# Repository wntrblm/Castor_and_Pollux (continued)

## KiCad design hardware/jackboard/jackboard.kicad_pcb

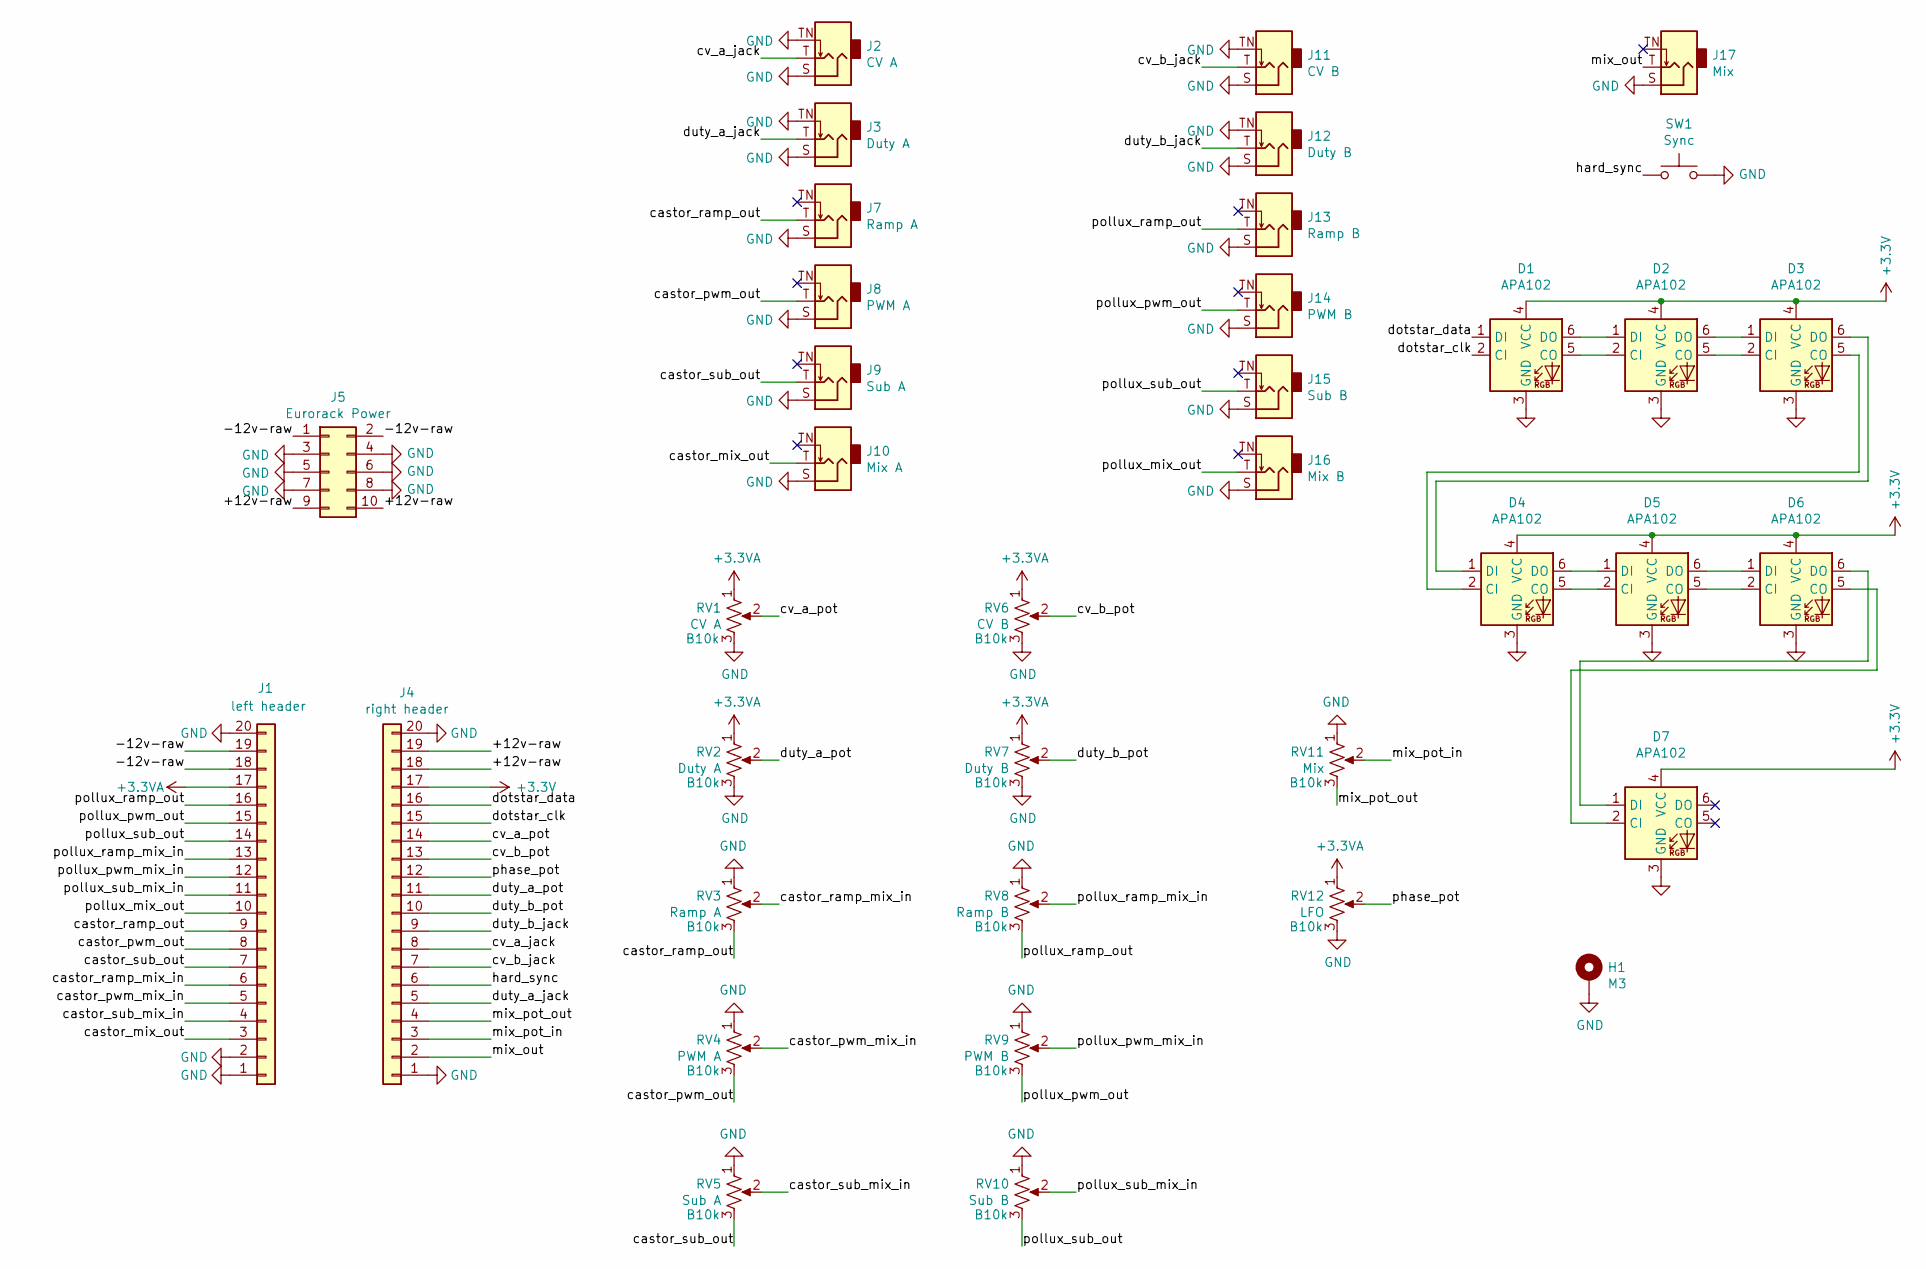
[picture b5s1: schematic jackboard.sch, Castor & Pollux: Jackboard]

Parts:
D1, D2, D3, D4, D5, D6, D7: APA102; LED_RGB_5050-6
H1: M3; MountingHole_3.2mm_M3_Pad_Via
J1: left header; PinHeader_1x20_P2.54mm_Vertical
J2: CV A; WQP-WQP518MA
J3: Duty A; WQP-WQP518MA
J4: right header; PinHeader_1x20_P2.54mm_Vertical
J5: Eurorack Power; 2X5-SHROUDED_LOCK
J7: Ramp A; WQP-WQP518MA
J8: PWM A; WQP-WQP518MA
J9: Sub A; WQP-WQP518MA
J10: Mix A; WQP-WQP518MA
J11: CV B; WQP-WQP518MA
J12: Duty B; WQP-WQP518MA
J13: Ramp B; WQP-WQP518MA
J14: PWM B; WQP-WQP518MA
J15: Sub B; WQP-WQP518MA
J16: Mix B; WQP-WQP518MA
J17: Mix; WQP-WQP518MA
RV1: CV A; Alpha_Pot
RV2: Duty A; Alpha_Pot
RV3: Ramp A; Alpha_Pot
RV4: PWM A; Alpha_Pot
RV5: Sub A; Alpha_Pot
RV6: CV B; Alpha_Pot
RV7: Duty B; Alpha_Pot
RV8: Ramp B; Alpha_Pot
RV9: PWM B; Alpha_Pot
RV10: Sub B; Alpha_Pot
RV11: Mix; Alpha_Pot
RV12: LFO; Alpha_Pot
SW1: Sync; SW_PUSH_6mm

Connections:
+3.3VA: J1.17, RV1.1, RV2.1, RV6.1, RV7.1, RV12.1
+3V3: D1.4 (VCC), D2.4 (VCC), D3.4 (VCC), D4.4 (VCC), D5.4 (VCC), D6.4 (VCC), D7.4 (VCC), J4.17
/+12v-raw: J4.18, J4.19, J5.9, J5.10
/-12v-raw: J1.18, J1.19, J5.1, J5.2
/castor_mix_out: J1.3, J10.T
/castor_pwm_mix_in: J1.5, RV4.2
/castor_pwm_out: J1.8, J8.T, RV4.3
/castor_ramp_mix_in: J1.6, RV3.2
/castor_ramp_out: J1.9, J7.T, RV3.3
/castor_sub_mix_in: J1.4, RV5.2
/castor_sub_out: J1.7, J9.T, RV5.3
/cv_a_jack: J2.T, J4.8
/cv_a_pot: J4.14, RV1.2
/cv_b_jack: J4.7, J11.T
/cv_b_pot: J4.13, RV6.2
/dotstar_clk: D1.2 (CI), J4.15
/dotstar_data: D1.1 (DI), J4.16
/duty_a_jack: J3.T, J4.5
/duty_a_pot: J4.11, RV2.2
/duty_b_jack: J4.9, J12.T
/duty_b_pot: J4.10, RV7.2
/hard_sync: J4.6, SW1.1
/mix_out: J4.2, J17.T
/mix_pot_in: J4.3, RV11.2
/mix_pot_out: J4.4, RV11.3
/phase_pot: J4.12, RV12.2
/pollux_mix_out: J1.10, J16.T
/pollux_pwm_mix_in: J1.12, RV9.2
/pollux_pwm_out: J1.15, J14.T, RV9.3
/pollux_ramp_mix_in: J1.13, RV8.2
/pollux_ramp_out: J1.16, J13.T, RV8.3
/pollux_sub_mix_in: J1.11, RV10.2
/pollux_sub_out: J1.14, J15.T, RV10.3
GND: D1.3 (GND), D2.3 (GND), D3.3 (GND), D4.3 (GND), D5.3 (GND), D6.3 (GND), D7.3 (GND), H1.1, J1.1, J1.2, J1.20, J2.S, J2.TN, J3.S, J3.TN, J4.1, J4.20, J5.3, J5.4, J5.5, J5.6, J5.7, J5.8, J7.S, J8.S, J9.S, J10.S, J11.S, J11.TN, J12.S, J12.TN, J13.S, J14.S, J15.S, J16.S, J17.S, RV1.3, RV2.3, RV3.1, RV4.1, RV5.1, RV6.3, RV7.3, RV8.1, RV9.1, RV10.1, RV11.1, RV12.3, SW1.2
unnamed: D1.5 (CO), D2.2 (CI)
unnamed: D1.6 (DO), D2.1 (DI)
unnamed: D2.5 (CO), D3.2 (CI)
unnamed: D2.6 (DO), D3.1 (DI)
unnamed: D3.5 (CO), D4.2 (CI)
unnamed: D3.6 (DO), D4.1 (DI)
unnamed: D4.5 (CO), D5.2 (CI)
unnamed: D4.6 (DO), D5.1 (DI)
unnamed: D5.5 (CO), D6.2 (CI)
unnamed: D5.6 (DO), D6.1 (DI)
unnamed: D6.5 (CO), D7.2 (CI)
unnamed: D6.6 (DO), D7.1 (DI)

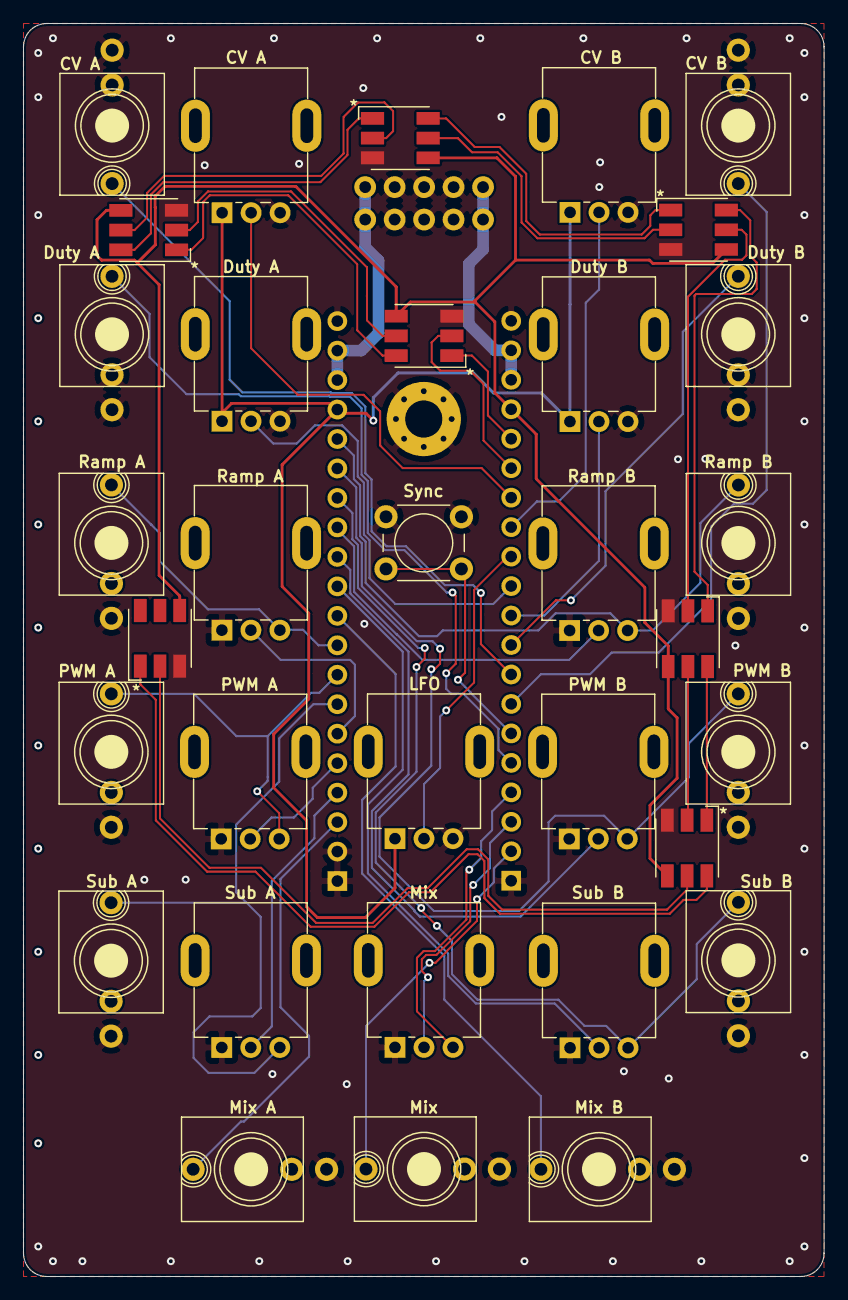
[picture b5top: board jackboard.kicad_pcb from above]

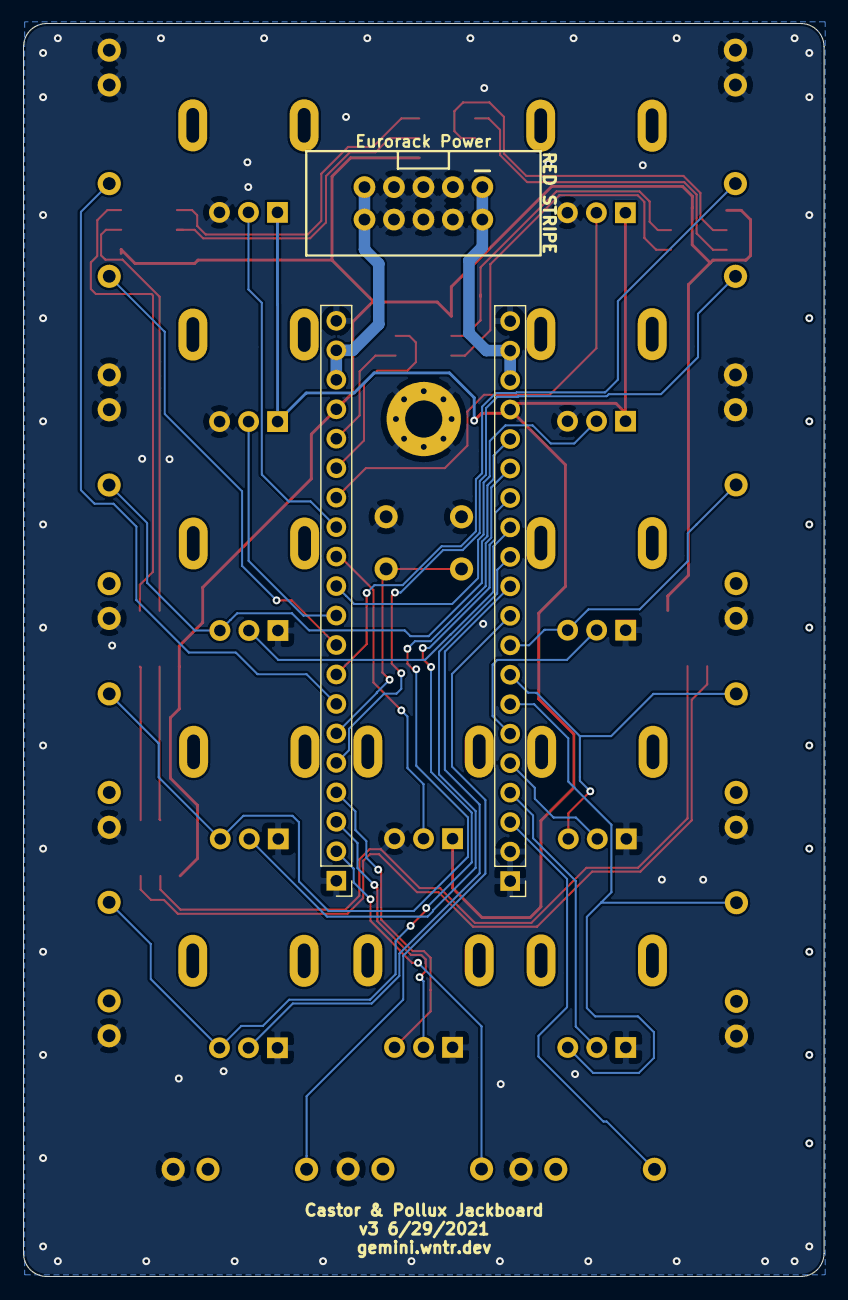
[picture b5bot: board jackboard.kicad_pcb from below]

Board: 2 copper layers, 69.0 x 108.0 mm, 37 parts (3 on the bottom side), 46 nets.

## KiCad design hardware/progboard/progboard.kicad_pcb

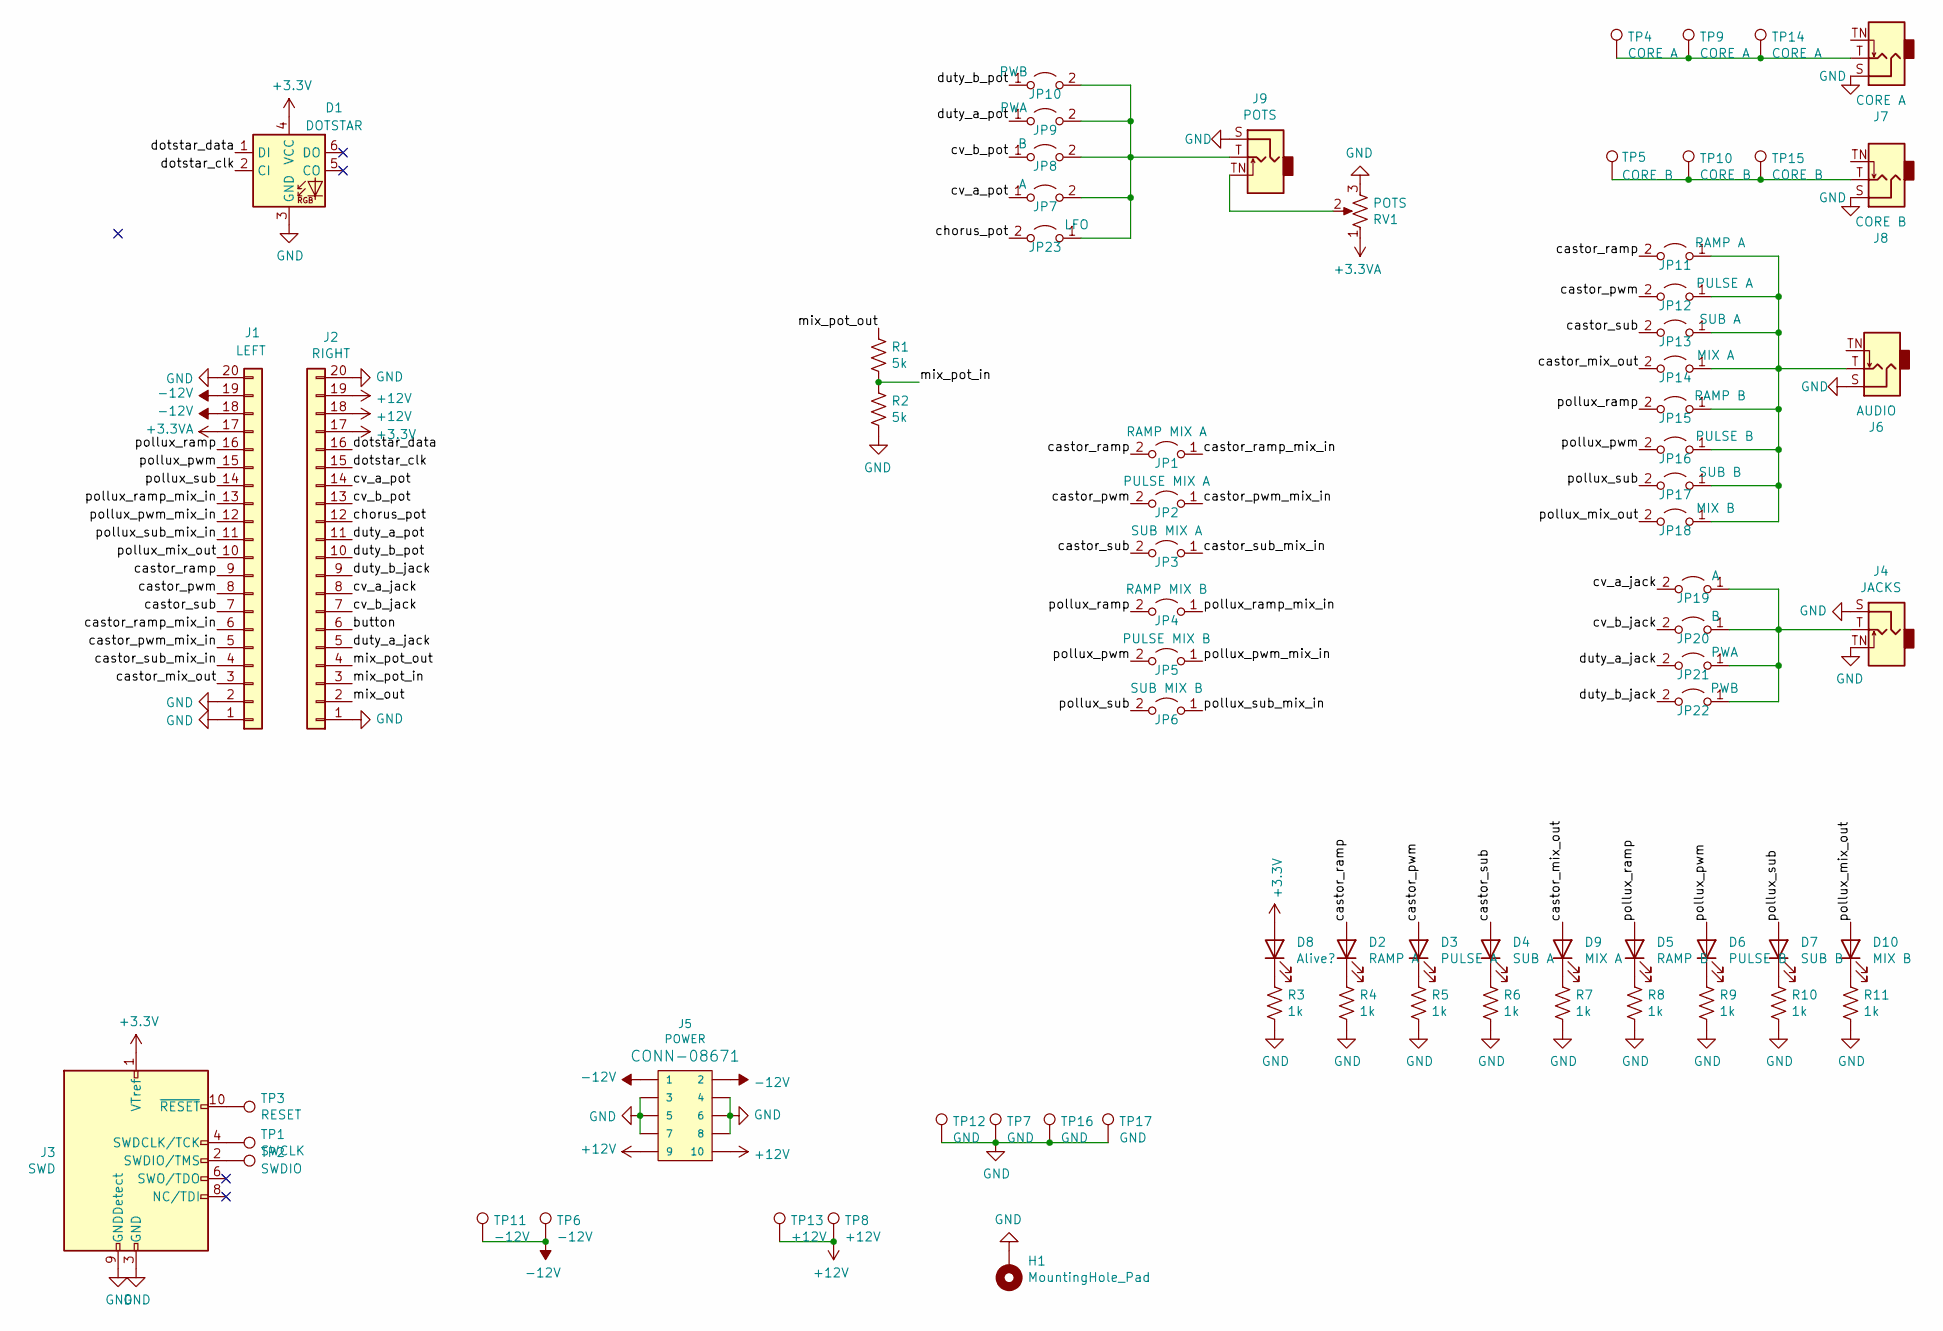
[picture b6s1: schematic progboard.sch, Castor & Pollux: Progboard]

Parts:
D1: DOTSTAR; LED_RGB_5050-6
D2: RAMP A; LED_D5.0mm
D3: PULSE A; LED_D5.0mm
D4: SUB A; LED_D5.0mm
D5: RAMP B; LED_D5.0mm
D6: PULSE B; LED_D5.0mm
D7: SUB B; LED_D5.0mm
D8: Alive?; LED_D5.0mm
D9: MIX A; LED_D5.0mm
D10: MIX B; LED_D5.0mm
H1: MountingHole_Pad; MountingHole_3.2mm_M3_Pad_Via
J1: LEFT; PinSocket_1x20_P2.54mm_Vertical
J2: RIGHT; PinSocket_1x20_P2.54mm_Vertical
J3: SWD; PinHeader_2x05_P1.27mm_Vertical
J4: JACKS; WQP-PJ301M-12_JACK
J5: POWER; 2X5-SHROUDED_LOCK
J6: AUDIO; WQP-PJ301M-12_JACK
J7: CORE A; WQP-PJ301M-12_JACK
J8: CORE B; WQP-PJ301M-12_JACK
J9: POTS; WQP-PJ301M-12_JACK
JP1: RAMP MIX A; TestPoint_2Pads_Pitch2.54mm_Drill0.8mm
JP2: PULSE MIX A; TestPoint_2Pads_Pitch2.54mm_Drill0.8mm
JP3: SUB MIX A; TestPoint_2Pads_Pitch2.54mm_Drill0.8mm
JP4: RAMP MIX B; TestPoint_2Pads_Pitch2.54mm_Drill0.8mm
JP5: PULSE MIX B; TestPoint_2Pads_Pitch2.54mm_Drill0.8mm
JP6: SUB MIX B; TestPoint_2Pads_Pitch2.54mm_Drill0.8mm
JP7, JP19: A; TestPoint_2Pads_Pitch2.54mm_Drill0.8mm
JP8, JP20: B; TestPoint_2Pads_Pitch2.54mm_Drill0.8mm
JP9, JP21: PWA; TestPoint_2Pads_Pitch2.54mm_Drill0.8mm
JP10, JP22: PWB; TestPoint_2Pads_Pitch2.54mm_Drill0.8mm
JP11: RAMP A; TestPoint_2Pads_Pitch2.54mm_Drill0.8mm
JP12: PULSE A; TestPoint_2Pads_Pitch2.54mm_Drill0.8mm
JP13: SUB A; TestPoint_2Pads_Pitch2.54mm_Drill0.8mm
JP14: MIX A; TestPoint_2Pads_Pitch2.54mm_Drill0.8mm
JP15: RAMP B; TestPoint_2Pads_Pitch2.54mm_Drill0.8mm
JP16: PULSE B; TestPoint_2Pads_Pitch2.54mm_Drill0.8mm
JP17: SUB B; TestPoint_2Pads_Pitch2.54mm_Drill0.8mm
JP18: MIX B; TestPoint_2Pads_Pitch2.54mm_Drill0.8mm
JP23: LFO; TestPoint_2Pads_Pitch2.54mm_Drill0.8mm
R1, R2: 5k; R_Axial_DIN0207_L6.3mm_D2.5mm_P7.62mm_Horizontal
R3, R4, R5, R6, R7, R8, R9, R10, R11: 1k; R_Axial_DIN0207_L6.3mm_D2.5mm_P7.62mm_Horizontal
RV1: POTS; Alpha_Pot
TP1: SWCLK; TestPoint_THTPad_D1.5mm_Drill0.7mm
TP2: SWDIO; TestPoint_THTPad_D1.5mm_Drill0.7mm
TP3: RESET; TestPoint_THTPad_D1.5mm_Drill0.7mm
TP4: CORE A; TestPoint_THTPad_D1.5mm_Drill0.7mm
TP5: CORE B; TestPoint_THTPad_D1.5mm_Drill0.7mm
TP6: -12V; TestPoint_Plated_Hole_D3.0mm
TP7, TP16, TP17: GND; TestPoint_Plated_Hole_D3.0mm
TP8: +12V; TestPoint_Plated_Hole_D3.0mm
TP9: CORE A; TestPoint_Plated_Hole_D3.0mm
TP10: CORE B; TestPoint_Plated_Hole_D3.0mm
TP11: -12V; PinHeader_1x01_P2.54mm_Vertical
TP12: GND; PinHeader_1x01_P2.54mm_Vertical
TP13: +12V; PinHeader_1x01_P2.54mm_Vertical
TP14: CORE A; PinHeader_1x01_P2.54mm_Vertical
TP15: CORE B; PinHeader_1x01_P2.54mm_Vertical

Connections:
+3.3VA: J1.17, RV1.1
+3V3: D1.4 (VCC), D8.2 (A), J2.17, J3.1 (VTref)
+12V: J2.18, J2.19, J5.9, J5.10, TP8.1, TP13.1
-12V: J1.18, J1.19, J5.1, J5.2, TP6.1, TP11.1
/button: J2.6
/castor_mix_out: D9.2 (A), J1.3, JP14.2 (B)
/castor_pwm: D3.2 (A), J1.8, JP2.2 (B), JP12.2 (B)
/castor_pwm_mix_in: J1.5, JP2.1 (A)
/castor_ramp: D2.2 (A), J1.9, JP1.2 (B), JP11.2 (B)
/castor_ramp_mix_in: J1.6, JP1.1 (A)
/castor_sub: D4.2 (A), J1.7, JP3.2 (B), JP13.2 (B)
/castor_sub_mix_in: J1.4, JP3.1 (A)
/chorus_pot: J2.12, JP23.2 (B)
/cv_a_jack: J2.8, JP19.2 (B)
/cv_a_pot: J2.14, JP7.1 (A)
/cv_b_jack: J2.7, JP20.2 (B)
/cv_b_pot: J2.13, JP8.1 (A)
/dotstar_clk: D1.2 (CI), J2.15
/dotstar_data: D1.1 (DI), J2.16
/duty_a_jack: J2.5, JP21.2 (B)
/duty_a_pot: J2.11, JP9.1 (A)
/duty_b_jack: J2.9, JP22.2 (B)
/duty_b_pot: J2.10, JP10.1 (A)
/mix_out: J2.2
/mix_pot_in: J2.3, R1.2, R2.1
/mix_pot_out: J2.4, R1.1
/pollux_mix_out: D10.2 (A), J1.10, JP18.2 (B)
/pollux_pwm: D6.2 (A), J1.15, JP5.2 (B), JP16.2 (B)
/pollux_pwm_mix_in: J1.12, JP5.1 (A)
/pollux_ramp: D5.2 (A), J1.16, JP4.2 (B), JP15.2 (B)
/pollux_ramp_mix_in: J1.13, JP4.1 (A)
/pollux_sub: D7.2 (A), J1.14, JP6.2 (B), JP17.2 (B)
/pollux_sub_mix_in: J1.11, JP6.1 (A)
GND: D1.3 (GND), H1.1, J1.1, J1.2, J1.20, J2.1, J2.20, J3.3 (GND), J3.5 (GND), J3.9 (GNDDetect), J4.S, J4.TN, J5.3, J5.4, J5.5, J5.6, J5.7, J5.8, J6.S, J7.S, J8.S, J9.S, R2.2, R3.2, R4.2, R5.2, R6.2, R7.2, R8.2, R9.2, R10.2, R11.2, RV1.3, TP7.1, TP12.1, TP16.1, TP17.1
unnamed: D2.1 (K), R4.1
unnamed: D3.1 (K), R5.1
unnamed: D4.1 (K), R6.1
unnamed: D5.1 (K), R8.1
unnamed: D6.1 (K), R9.1
unnamed: D7.1 (K), R10.1
unnamed: D8.1 (K), R3.1
unnamed: D9.1 (K), R7.1
unnamed: D10.1 (K), R11.1
unnamed: J3.2 (SWDIO/TMS), TP2.1
unnamed: J3.4 (SWDCLK/TCK), TP1.1
unnamed: J3.10 (~RESET~), TP3.1
unnamed: J4.T, JP19.1 (A), JP20.1 (A), JP21.1 (A), JP22.1 (A)
unnamed: J6.T, JP11.1 (A), JP12.1 (A), JP13.1 (A), JP14.1 (A), JP15.1 (A), JP16.1 (A), JP17.1 (A), JP18.1 (A)
unnamed: J7.T, TP4.1, TP9.1, TP14.1
unnamed: J8.T, TP5.1, TP10.1, TP15.1
unnamed: J9.T, JP7.2 (B), JP8.2 (B), JP9.2 (B), JP10.2 (B), JP23.1 (A)
unnamed: J9.TN, RV1.2

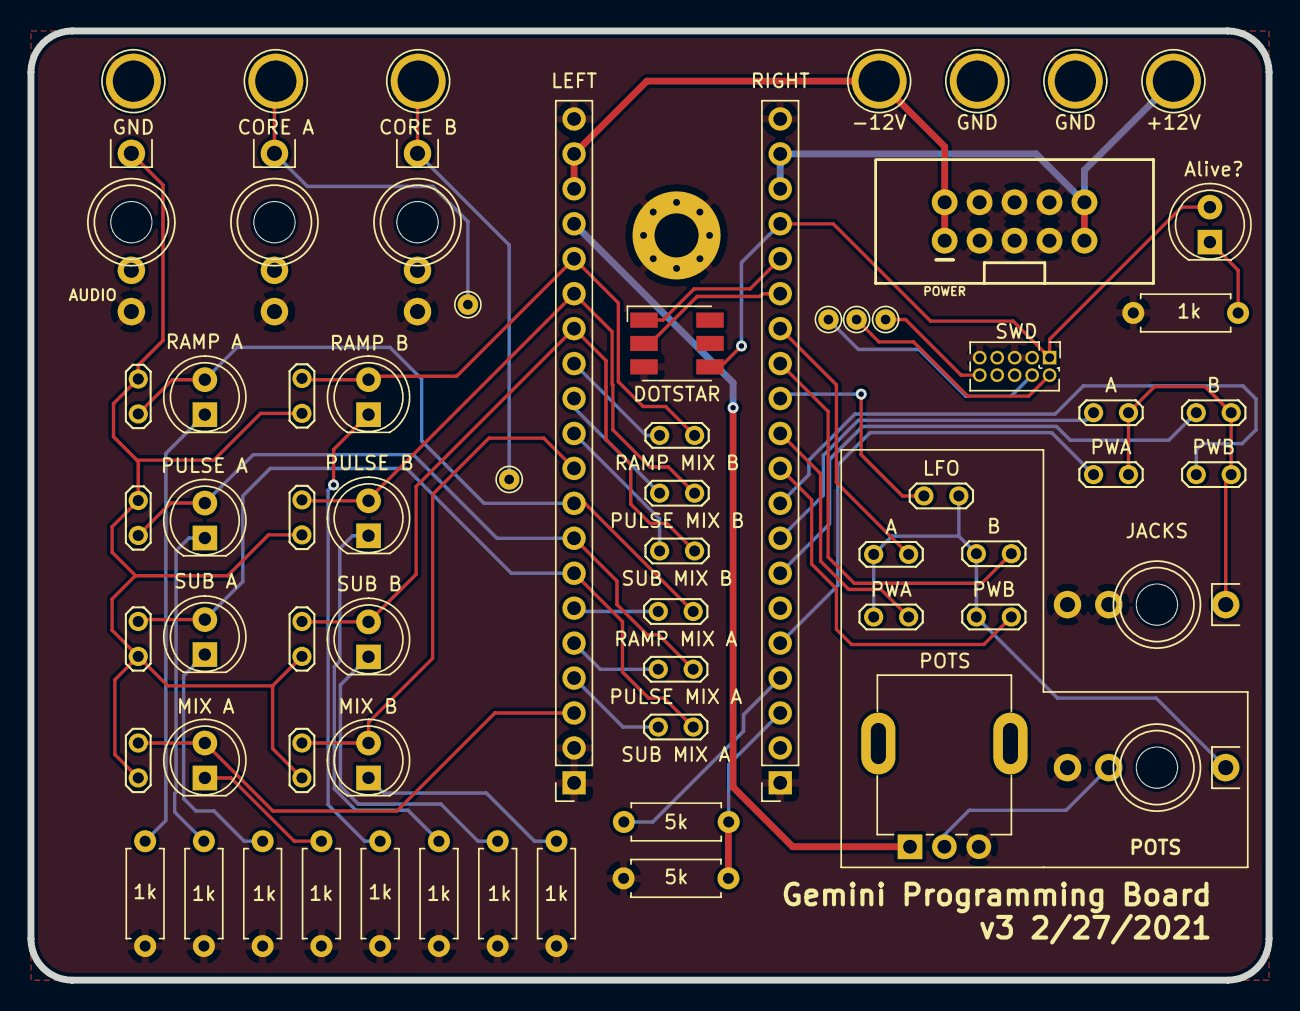
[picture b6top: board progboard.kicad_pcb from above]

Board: 2 copper layers, 90.0 x 69.0 mm, 67 parts (0 on the bottom side), 50 nets.

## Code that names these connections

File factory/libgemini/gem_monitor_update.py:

# Hey this file was generated by Structy from
# gem_monitor_update.structy. Maybe don't edit it!

from dataclasses import dataclass
from typing import ClassVar

import structy


@dataclass
class GemMonitorUpdate(structy.Struct):
    _PACK_STRING : ClassVar[str] = "B?HHHHHHHHBiHIHHHHHHHiBiHIHHHH"

    PACKED_SIZE : ClassVar[int] = 66
    """The total size of the struct once packed."""

    mode: int = 0

    tweaking: bool = False

    lfo_knob: int = 0

    tweak_lfo_knob: int = 0

    castor_pitch_knob: int = 0

    castor_pitch_cv: int = 0

    castor_pulse_knob: int = 0

    castor_pulse_cv: int = 0

    castor_tweak_pitch_knob: int = 0

    castor_tweak_pulse_knob: int = 0

    castor_pitch_behavior: int = 0

    castor_pitch: structy.Fix16 = 0

    castor_pulse_width: int = 0

    castor_period: int = 0

    castor_ramp: int = 0

    pollux_pitch_knob: int = 0

    pollux_pitch_cv: int = 0

    pollux_pulse_knob: int = 0

    pollux_pulse_cv: int = 0

    pollux_tweak_pitch_knob: int = 0

    pollux_tweak_pulse_knob: int = 0

    pollux_reference_pitch: structy.Fix16 = 0

    pollux_pitch_behavior: int = 0

    pollux_pitch: structy.Fix16 = 0

    pollux_pulse_width: int = 0

    pollux_period: int = 0

    pollux_ramp: int = 0

    loop_time: int = 0

    animation_time: int = 0

    sample_time: int = 0

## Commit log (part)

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2021-03-03 Docs: update the settings editor page and remove the warning about it not yet being available
2021-03-03 Deployed 51c37af with MkDocs version: 1.1.2
2021-03-23 Fix broken anchor link
2021-03-23 Deployed bac1b1a with MkDocs version: 1.1.2
2021-04-09 factory: Small tweaks to the monitor and calibration scripts.
2021-04-14 Deployed b569311 with MkDocs version: 1.1.2
2021-04-14 Deployed 467ea37 with MkDocs version: 1.1.2
2021-04-21 user_guide: Use WinterJS for the settings editor.
2021-04-21 hardware: added values & datasheet for pots in schematic
2021-04-21 firmware: Remove unneeded change to NVM configuration from gem_nvm_init, as its done in Reset_Handler
2021-04-21 hardware: added values & datasheet for pots in schematic (#13)
2021-04-21 Deployed f28f320 with MkDocs version: 1.1.2
2021-04-22 firmware: Update firmware to work with latest libwinter
2021-04-22 firmware: Move gem_fuses to libwinter/samd/samd21/wntr_fuses.c
2021-04-22 firmware: fix incorrect port for TCC1, introduced in 569202325
2021-04-22 factory: auto-update firmware when using monitor
2021-04-29 Deployed ecc23fc with MkDocs version: 1.1.2
2021-04-30 Correcting Tag-Connect product link (#15)
2021-05-08 user guide: Update to new styles, re-layout the settings editor
2021-05-16 firmware: Fixup tests and tidy
2021-05-19 Update index.md
    Fix minor word error: and -> at.
2021-05-19 fix typo (#18)
    assembled -> assembly in Castor & Pollux user guide
2021-05-19 Update index.md (#17)
    * Update index.md
    Fix minor word error: and -> at.
    * Update index.md
2021-05-25 docs: fix audio playback on Safari 14.1+
2021-05-26 hardware: Add a jig for the programming board
2021-06-03 Deployed ea36798 with MkDocs version: 1.1.2
2021-06-05 Remove unused constant
2021-06-09 Deployed 635f914 with MkDocs version: 1.1.2
2021-06-09 Deployed c1a07bb with MkDocs version: 1.1.2
2021-06-10 Deployed 78d6d33 with MkDocs version: 1.1.2
2021-06-10 user guide: Make settings editor be more resilient to WebMIDI quirks around SysEx messages.
2021-06-13 hardware: assign new MPNs for mainboard BOM
2021-06-14 hardware: mark version 4 of the mainboard
2021-06-19 user guide: Update mkdocs external link plugin
2021-06-19 factory: add --force-update option to monitor
2021-06-20 factory: Remove unused reset_knob_ranges.py script
2021-06-21 hardware: export mainboard PDF in black & white to avoid KiCAD color issues
2021-06-21 Update waveshape link to waveshapes
    Update waveshape link to waveshapes
2021-06-21 Update waveshape link to waveshapes (#19)
    Update waveshape link to waveshapes
2021-06-21 user guide: Fix bad version for mkdocs-include-markdown-plugin in requirements.txt
2021-07-08 hardware: Remove unneeded parts on the jackboard
2021-07-13 user guide: add note about no-clean flux
2021-08-21 Fix link in releasing script
2021-08-31 user guide: Update settings editor for new LFO features
    - Updated winterjs' forms and utils.
    - Modified waveforms.js to support new winterjs forms.
    - Added LFO fields to the settings editor.
    - Added LFO waveshape display to the settings editor.
2021-08-31 user guide: Fix firmware date check in settings editor.
2021-09-13 factory: Save full ADC/AFE measurement data
2021-09-19 firmware: Change 'set dac' SysEx command to set all four channels at once instead of just one at a time
2021-09-19 firmware: print SysEx commands in debug mode
2021-09-20 hardware: prepare testkit adapter for manufacturing
2021-09-20 firmware: Fix unused variable warning when using debug_printf
2021-09-21 Deployed 69775f5 with MkDocs version: 1.2.2
2021-10-01 user guide: fix string comparison for midi device names
2021-10-08 Fix typos in "CV smoothing" settings description (#23)
2021-10-26 Add basic panel without Winterbloom branding
2021-12-08 hardware/testkit-adapter: Add laser designs for pin holder, board guide, and pressure plate
2021-12-16 firmware: small update to format strings in wntr_midi_core
2021-12-27 user guide: update to latest theme and winterjs
2022-01-03 factory: change Hubble LEDs during factory setup
2022-02-03 meta: update user guide publishing script to match the other modules
2022-02-20 user guide: fix some grammar issues (#27)
2022-04-04 firmware: Add pitch CV quantizer logic
    Note: For now, the scale cannot be chosen. The input is always quantized
    to the nearest 12-tone equal temperament step.
2022-04-04 User guide: Fix layout of quantizer settings description
    The version of the description added in the previous patch was
    marked up wrong, resulting in the text appearing in two separate
    boxes rather than one box with two paragraphs inside it.
    This patch fixes that issue.
2022-04-23 Install rtmidi for all steps
2022-04-23 Skip smoothstep when quantization is active
2022-04-23 firmware: Change quantizer to use a scale stored in a table
2022-04-23 Bugfix for linker script
    The previous commits needed more stack size than was previously allocated,
    and changed the STACK_SIZE variable in configure.py accordingly.
    Strangely, however, the linker still only allocated 2KB to the stack.
    On further investigation, the line
    STACK_SIZE = DEFINED(__stack_size__) ? __stack_size__ : 0x800;
    doesn't work, it always sets STACK_SIZE to 0x800. But changing it to
2022-04-23 firmware: Store quantizer table in flash
2022-05-11 factory: don't print report if not all steps are run
2022-07-06 Fix bug in teeth where dirty data at the end of the destination buffer would cause invalid sysex messages
2022-07-06 Add firmware support for pulse width bitmasking
    This allows emulating the old behavior before the DAC refresh rate was fixed.
2022-07-06 Add pulse width behavior settings
    Also changes the behavior of the "save" button to automatically soft reset the module. Closes #28.
2022-07-06 Fixup firmware tests
2022-07-14 Remove jackboard
2022-07-15 Get DRC passing
2022-07-15 More small silkscreen cleanups
2022-07-15 Add USB notch, PCB specifications
2022-07-15 Swap ext connector for a vertical one
2022-07-15 Pull power traces onto one layer
2022-07-16 Progress on cleaning up the schematics
2022-07-16 Cleanup MCU schematic
2022-07-17 Clear ERC
2022-07-17 Reannotate schematic
2022-07-18 Switch audio filter caps to 0603. Start auditing BOM
2022-07-18 Switch EXT header to a 2x5 1.27mm pitch IDC header
2022-07-19 Finalize resistor mpns
2022-07-26 * Added versions strapping pins * Added VBUS power * Filled out regulator thermal calculations
2022-08-05 hardware: Updated jack footprints so they have f.fab markings
2022-08-06 firmware: Add pin-based hardware revision determination
2022-08-06 hardware: note correct waveform outputs for TCC
2022-08-06 hardware: ignore kicad_prl files
2022-08-06 hardware: remove unused 3dmodels
2022-08-07 hardware: add fancy labels
2022-08-08 hardware: fixup schematic fields
2022-08-08 hardware: minor tweaks to power schematic's layout
2022-08-08 hardware: use winterbloom footprints for C, R, and L
2022-08-09 firmware: Adjust ADC input range for V5
2022-08-10 hardware: spruce up some labels
2022-09-22 user guide: Fix LFO waveform 2 shape control
2022-09-26 hardware: update some labels, fix some fields, re-do fancytext
2022-09-26 hardware: wire an ADC pin to 3v3 for self-calibration
2022-10-08 Add expander
2022-10-08 Remove unused progboard, panel
2022-10-20 Adjust ADC configuration to bump effective sample rate from 1.5 kHz to 5 kHz.
2022-10-20 Fixup tests
2022-10-22 firmware: fix pinmux name in libwinter
2022-10-22 firmware: put gem_mcp4728 update into RAM
2022-10-22 firmware: remove the voltage to timer period table, refactor table access code
2022-10-22 firmware: use new pulseout and ramp lookup table methods
2022-10-23 firmware: add sysex command 0x20 for setting the frequency of an oscillator, remove sysex command 0x06 for setting the period.
2022-10-24 hardware: Aadd expander and hubble lens
2022-10-24 factory: merge in changes from main
2022-10-31 firmware: Fix ADC channel order
2022-11-04 firmware: Add SystemInit() to startup_samd21
2023-02-26 Add new hubble lens board guide
2023-02-26 Update mainboard schematic files to KiCAD 7
2023-03-14 Updating factory scripts to support v2 board and hubble lens
2023-03-20 hardware: add interposer board
2023-03-20 firmware: refactoring and preparing for modal interface
2023-03-21 firmware: improve mode switch animation and idle animation, use lfo value to control sparkle rate
2023-03-23 firmware: Keep track of the waveform amplitude in wntr_periodic_waveform
2023-03-23 firmware: pass tweaking state in gem_led_animation
2023-03-23 firmware: fixup configure script for tests
2023-03-23 firmware: add settings V5 placeholder
2023-03-23 firmware: overhaul main.c and implement better tweak overlay controls
2023-03-24 firmware: revise monitor update message
2023-03-24 factory: add clock calibration script
2023-03-24 factory: add clock calibration to factory_setup
2023-03-25 user guide: update settings editor with new settings
2023-03-25 firmware: make animations for each mode distinct
2023-03-27 user guide: initial work on updating docs for C&PII, added new illustrations
2023-03-28 user guide: add more illustrations
2023-03-28 user guide: update illustrations
2023-03-29 firmware: add LED configuration for C&PI
2023-03-29 firmware: configuration fixes for rev4 boards
2023-03-30 firmware: add hardware revision to get_serial_number sysex command
2023-04-02 user guide: fix a few minor copy issues
2023-04-02 factory: fix calculation of pitch offset
2023-04-03 user guide: add new kit build photos
2023-04-03 user guide: finish up build guide for C&P II
2023-04-05 firmware: Increase the FM deadzone to avoid FM still being applied even when the knob is fully CCW
2023-04-22 user guide: add Vale configuration
2023-04-22 Enable GHA for v2 branch
2023-04-22 Settings editor: Update minimum supported firmware version
2023-05-02 settings editor: fix minimum firmware version
2023-05-18 user guide: fix small typo
2023-09-11 setting editor: add monitoring to help with troubleshooting
2023-10-16 settings editor: fix ADC channel used for CV calibration
2024-02-07 firmware: Remove channel swap for SysEx set frequency
2024-02-10 firmware: Fix issue with fix16 rounding causing pitch glitches
2024-02-10 firmware: fix formatting
2024-02-11 meta: update github actions for building the firmware
2024-02-11 meta: fixup github actions
2024-02-28 user guide: disambiguate "manual" from "guide".
2024-02-28 user guide: fix mkdocs link warning
2024-07-31 factory: adjust firmware programming to accomodate partially programmed units
2025-01-26 User guide: update calibratons to pull from github instead of cloud storage
2025-01-30 Hardware: added faceplates for v1, v2, and the expander
2025-04-26 update mainboard to kicad 9
2025-04-26 update expander faceplate to kicad 9
2025-04-26 update faceplate-2 to kicad 9
2025-04-26 update interposer to kicad 9
2025-04-29 Update hardware designs to KiCad 9 (#32)
    * update mainboard to kicad 9
    * update expander to kicad 9
    * update expander faceplate to kicad 9
    * update faceplate-1 to kicad 9
    * update faceplate-2 to kicad 9
    * update hubble-lens to kicad 9
2025-09-22 docs: Create BASIC_FLASH_GUIDE.md (#33)
    This is based on the steps I followed when flashing my Castor and Pollux boards.
    I don't have the ability to verify if these steps work with Apple hardware of any description, but they should hopefully be similar enough to be usable.
